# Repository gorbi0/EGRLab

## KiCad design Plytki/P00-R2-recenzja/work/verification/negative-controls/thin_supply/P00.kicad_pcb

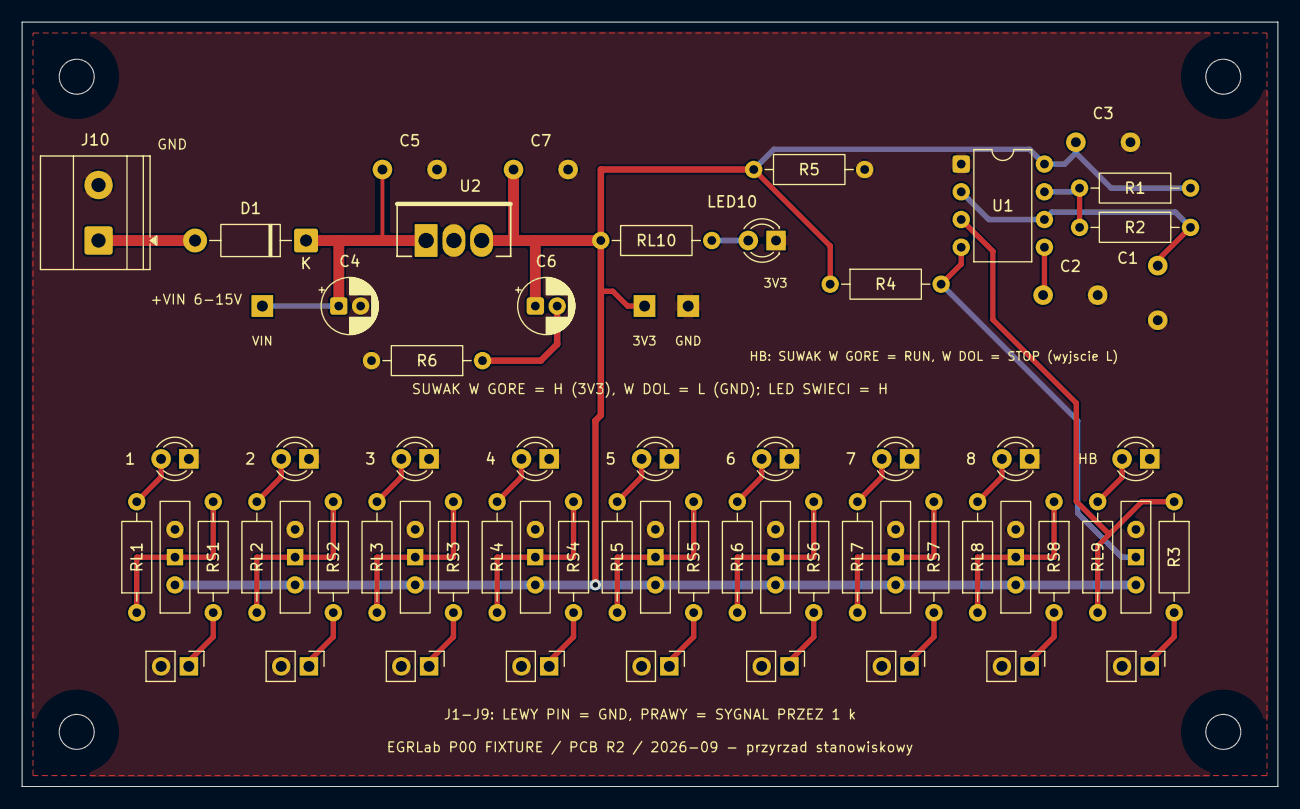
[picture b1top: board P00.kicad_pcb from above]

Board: 2 copper layers, 115.0 x 70.0 mm, 70 parts (0 on the bottom side), 37 nets.

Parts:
C1, C3, C5, C7: 100nF / X7R; C_Vishay_K15_H5_P5
C2: 10nF / X7R; C_Vishay_K15_H5_P5
C4: 10u / 50V; CP_Radial_D5.0mm_P2.00mm
C6: 22u / 50V; CP_Radial_D5.0mm_P2.00mm
D1: 1N5819; D_DO-41_SOD81_P10.16mm_Horizontal
H1, H2, H3, H4: M3 NPTH
J1: CH1 / pin header 1x2; PinHeader_1x02_P2.54mm_Vertical
J2: CH2 / pin header 1x2; PinHeader_1x02_P2.54mm_Vertical
J3: CH3 / pin header 1x2; PinHeader_1x02_P2.54mm_Vertical
J4: CH4 / pin header 1x2; PinHeader_1x02_P2.54mm_Vertical
J5: CH5 / pin header 1x2; PinHeader_1x02_P2.54mm_Vertical
J6: CH6 / pin header 1x2; PinHeader_1x02_P2.54mm_Vertical
J7: CH7 / pin header 1x2; PinHeader_1x02_P2.54mm_Vertical
J8: CH8 / pin header 1x2; PinHeader_1x02_P2.54mm_Vertical
J9: HEART / pin header 1x2; PinHeader_1x02_P2.54mm_Vertical
J10: VIN 6-15V / MKDS 2p; TerminalBlock_Phoenix_MKDS-1,5-2-5.08_1x02_P5.08mm_Horizont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
LED1: GREEN 3mm / CH1; LED_D3.0mm
LED2: GREEN 3mm / CH2; LED_D3.0mm
LED3: GREEN 3mm / CH3; LED_D3.0mm
LED4: GREEN 3mm / CH4; LED_D3.0mm
LED5: GREEN 3mm / CH5; LED_D3.0mm
LED6: GREEN 3mm / CH6; LED_D3.0mm
LED7: GREEN 3mm / CH7; LED_D3.0mm
LED8: GREEN 3mm / CH8; LED_D3.0mm
LED9: YELLOW 3mm / HEART; LED_D3.0mm
LED10: RED 3mm / 3V3; LED_D3.0mm
R1: 4K7 / 1%; R_Axial_DIN0207_L6.3mm_D2.5mm_P10.16mm_Horizontal
R2: 68K / 1%; R_Axial_DIN0207_L6.3mm_D2.5mm_P10.16mm_Horizontal
R3: 1K / 1%; R_Axial_DIN0207_L6.3mm_D2.5mm_P10.16mm_Horizontal
R4: 100K / 1%; R_Axial_DIN0207_L6.3mm_D2.5mm_P10.16mm_Horizontal
R5: 560R / 1%; R_Axial_DIN0207_L6.3mm_D2.5mm_P10.16mm_Horizontal
R6: 1R / 1%; R_Axial_DIN0207_L6.3mm_D2.5mm_P10.16mm_Horizontal
RL1, RL2, RL3, RL4, RL5, RL6, RL7, RL8, RL9, RL10: 1K / 1%; R_Axial_DIN0207_L6.3mm_D2.5mm_P10.16mm_Horizontal
RS1, RS2, RS3, RS4, RS5, RS6, RS7, RS8: 1K / 1%; R_Axial_DIN0207_L6.3mm_D2.5mm_P10.16mm_Horizontal
SW1: CH1 H/L; SW_Slide-03_Wuerth-WS-SLTV_10x2.5x6.4_P2.54mm
SW2: CH2 H/L; SW_Slide-03_Wuerth-WS-SLTV_10x2.5x6.4_P2.54mm
SW3: CH3 H/L; SW_Slide-03_Wuerth-WS-SLTV_10x2.5x6.4_P2.54mm
SW4: CH4 H/L; SW_Slide-03_Wuerth-WS-SLTV_10x2.5x6.4_P2.54mm
SW5: CH5 H/L; SW_Slide-03_Wuerth-WS-SLTV_10x2.5x6.4_P2.54mm
SW6: CH6 H/L; SW_Slide-03_Wuerth-WS-SLTV_10x2.5x6.4_P2.54mm
SW7: CH7 H/L; SW_Slide-03_Wuerth-WS-SLTV_10x2.5x6.4_P2.54mm
SW8: CH8 H/L; SW_Slide-03_Wuerth-WS-SLTV_10x2.5x6.4_P2.54mm
SW9: HEART RUN/STOP; SW_Slide-03_Wuerth-WS-SLTV_10x2.5x6.4_P2.54mm
TP1: V33; TestPad_1
TP2: GND; TestPad_1
TP3: VIN_P; TestPad_1
U1: TLC555CP; DIP-8_W7.62mm
U2: LM2937ET-3.3; TO220_3_P2.54_Drill1.4

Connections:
/P00_COUT_RET: C6.2, R6.1
/P00_CTRL: C2.1, U1.5
/P00_DIS: R1.2, R2.1, U1.7
/P00_HEART: J9.1, R3.2
/P00_LED1: LED1.2, RL1.2
/P00_LED2: LED2.2, RL2.2
/P00_LED3: LED3.2, RL3.2
/P00_LED4: LED4.2, RL4.2
/P00_LED5: LED5.2, RL5.2
/P00_LED6: LED6.2, RL6.2
/P00_LED7: LED7.2, RL7.2
/P00_LED8: LED8.2, RL8.2
/P00_LED_HB: LED9.2, RL9.2
/P00_LED_PWR: LED10.2, RL10.2
/P00_OSC: R3.1, RL9.1, U1.3
/P00_OUT1: J1.1, RS1.2
/P00_OUT2: J2.1, RS2.2
/P00_OUT3: J3.1, RS3.2
/P00_OUT4: J4.1, RS4.2
/P00_OUT5: J5.1, RS5.2
/P00_OUT6: J6.1, RS6.2
/P00_OUT7: J7.1, RS7.2
/P00_OUT8: J8.1, RS8.2
/P00_RC: C1.1, R2.2, U1.2, U1.6
/P00_RESET: R4.2, SW9.1, U1.4
/P00_S1: RL1.1, RS1.1, SW1.1
/P00_S2: RL2.1, RS2.1, SW2.1
/P00_S3: RL3.1, RS3.1, SW3.1
/P00_S4: RL4.1, RS4.1, SW4.1
/P00_S5: RL5.1, RS5.1, SW5.1
/P00_S6: RL6.1, RS6.1, SW6.1
/P00_S7: RL7.1, RS7.1, SW7.1
/P00_S8: RL8.1, RS8.1, SW8.1
/P00_V33: C3.1, C6.1, C7.1, R1.1, R4.1, R5.1, RL10.1, SW1.2, SW2.2, SW3.2, SW4.2, SW5.2, SW6.2, SW7.2, SW8.2, SW9.2, TP1.1, U1.8, U2.3
/P00_VIN: D1.2, J10.1
/P00_VIN_P: C4.1, C5.1, D1.1, TP3.1, U2.1
GND: C1.2, C2.2, C3.2, C4.2, C5.2, C7.2, J1.2, J2.2, J3.2, J4.2, J5.2, J6.2, J7.2, J8.2, J9.2, J10.2, LED1.1, LED2.1, LED3.1, LED4.1, LED5.1, LED6.1, LED7.1, LED8.1, LED9.1, LED10.1, R5.2, R6.2, SW1.3, SW2.3, SW3.3, SW4.3, SW5.3, SW6.3, SW7.3, SW8.3, SW9.3, TP2.1, U1.1, U2.2

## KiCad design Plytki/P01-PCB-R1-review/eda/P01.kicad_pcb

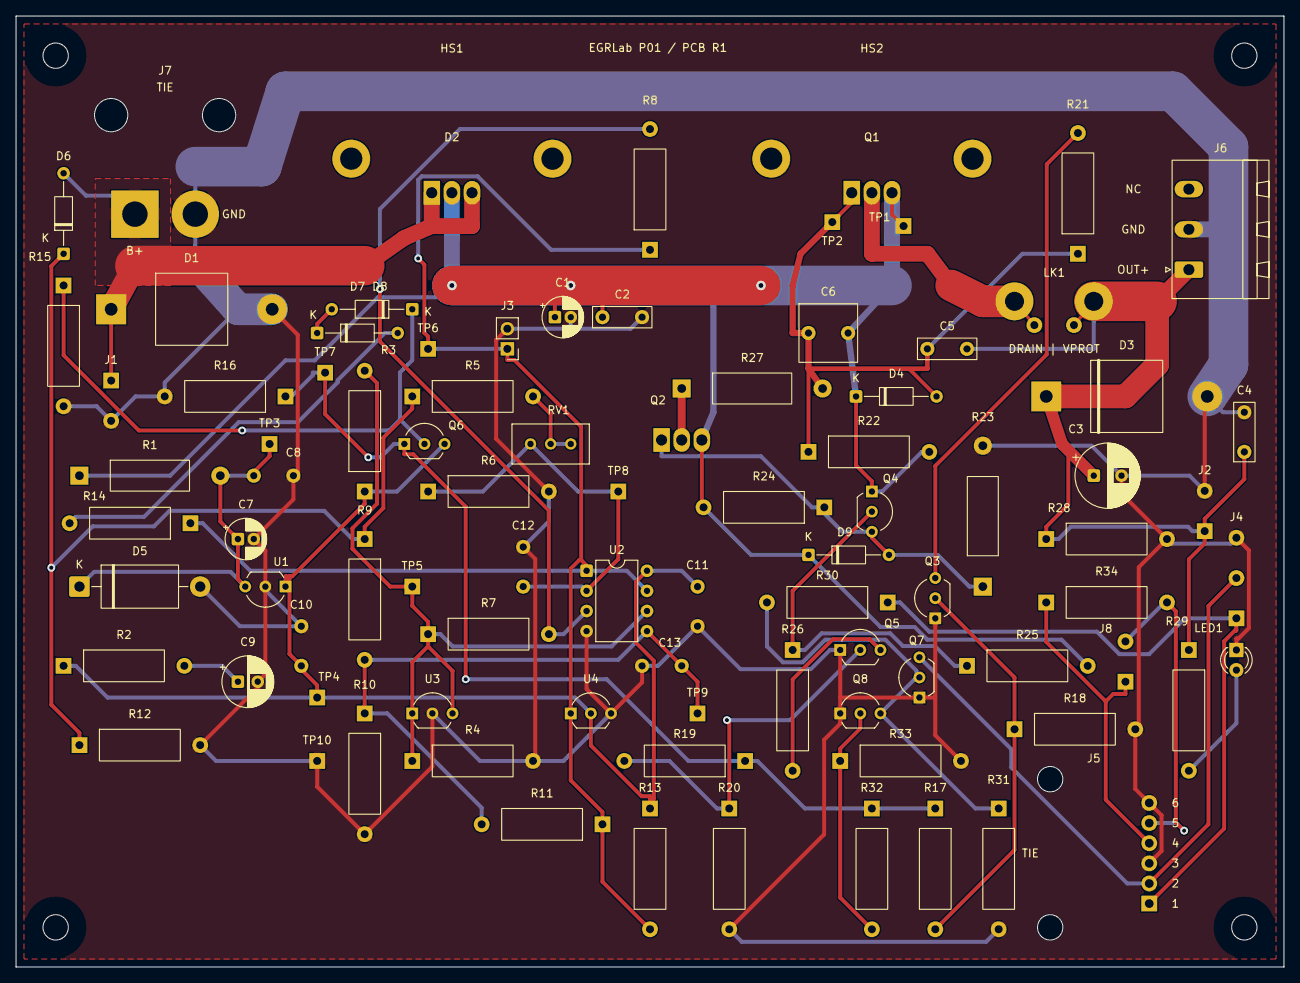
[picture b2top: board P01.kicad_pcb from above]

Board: 2 copper layers, 160.0 x 120.0 mm, 95 parts (0 on the bottom side), 34 nets.

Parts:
C1: 10u / 63V; CP_Radial_D5.0mm_P2.00mm
C2, C4: 100nF / 100V; C_TDK_B32529_L7.3_W2.5_P5
C3: 100u / 50V; CP_Radial_D8.0mm_P3.50mm
C5: 10nF / 100V; C_TDK_B32529_L7.3_W2.5_P5
C6: 1000nF / 100V; C_WIMA_MKS2_1u100V_L7.2_W7.2_P5
C7: 22u / 50V; CP_Radial_D5.0mm_P2.00mm
C8, C10, C11: 100nF / X7R; C_Vishay_K15_H5_P5
C9: 47u / 50V; CP_Radial_D6.3mm_P2.50mm
C12: 100pF / C0G; C_Vishay_K15_H5_P5
C13: 1nF / C0G; C_Vishay_K15_H5_P5
D1: 15KPA24CA; TVS_P600_BIDIR_P20.32
D2: STPS20100CT; TO220_3_P2.54_Drill1.4
D3: 5KP18A; TVS_P600_P20.32
D4: BZX55C15; D_DO-35_SOD27_P10.16mm_Horizontal
D5: 1.5KE18A-E3/54; D_DO-201_P15.24mm_Horizontal
D6, D7, D8: 1N4148; D_DO-35_SOD27_P10.16mm_Horizontal
D9: BZX55C15-TAP; D_DO-35_SOD27_P10.16mm_Horizontal
H1, H2, H3, H4: M3 NPTH
HS1, HS2: SK129-63STS; HS_Fischer_SK129_63.5_STS_D2.8
J1, J2, J8: TEST PADS; TestPads_2
J3: INHIBIT / SHORT=OFF; PinHeader_1x02_P2.54mm_Vertical
J4: TEST PADS; TestPads_3
J5: PG / soldered harness; Pigtail_PG_6xAWG22
J6: SUPPLY / MSTBA 3p; PhoenixContact_MSTBA_2,5_3-G-5,08_1x03_P5.08mm_Horizontal
J7: BAT / soldered wires; Pigtail_PWR_2x2.5mm2
LED1: GREEN 3mm; LED_D3.0mm
LK1: LINK / Cu 2.5mm2; Link_Kelvin_P10
Q1, Q2: SUP53P06-20-E3; TO220_3_P2.54_Drill1.4
Q3, Q5, Q6, Q7, Q8: 2N5551G; TO-92_Inline_Wide
Q4: 2N5401YBU; TO-92_Inline_Wide
R1: 150R / 2W; R_PR02_P17.78
R2: 1R / 0.5W; R_MFR50_H4_P15.24
R3: 820R / 0.5W; R_MFR50_H4_P15.24
R4, R16, R26, R30, R32: 10K / 0.5W; R_MFR50_H4_P15.24
R5: 54K9 / 0.1%; R_MFR50_H4_P15.24
R6, R7, R10: 10K / 0.1%; R_MFR50_H4_P15.24
R8: 220K / 0.1%; R_MFR50_H4_P15.24
R9: 26K1 / 0.1%; R_MFR50_H4_P15.24
R11: 249K / 0.1%; R_MFR50_H4_P15.24
R12, R15, R21, R24, R31: 100K / 0.5W; R_MFR50_H4_P15.24
R13: 2K2 / 0.5W; R_MFR50_H4_P15.24
R14, R17, R19, R28: 4K7 / 0.5W; R_MFR50_H4_P15.24
R18, R20, R25, R33: 47K / 0.5W; R_MFR50_H4_P15.24
R22: 470K / 0.5W; R_MFR50_H4_P15.24
R23: 2K2 / 2W; R_PR02_P17.78
R27: 10R / 2W; R_PR02_P17.78
R29: 6K8 / 0.5W; R_MFR50_H4_P15.24
R34: 0R / link; R_MFR50_H4_P15.24
RV1: 5K / 3296W; Potentiometer_Bourns_3296W_Vertical
TP1: VS; TestPad_1
TP2: GATE; TestPad_1
TP3: AUX_IN; TestPad_1
TP4: AUX5; TestPad_1
TP5: REF; TestPad_1
TP6: OK; TestPad_1
TP7: ENABLE; TestPad_1
TP8: OV_SENSE; TestPad_1
TP9: UV_SENSE; TestPad_1
TP10: GND; TestPad_1
U1: LM2936Z-5.0; TO-92_Inline_Wide
U2: LM2903P; DIP-8_W7.62mm
U3: TL431BILP; TO-92_Inline_Wide
U4: MCP120-450DI/TO; TO-92_Inline_Wide

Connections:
/AUX/P01_AUX_IN: C7.1, C8.1, D5.1, R1.2, TP3.1, U1.3
/AUX/P01_C_AUX_TOP: C9.1, R2.2
/AUX/P01_OV_REF: R7.2, R8.2, U2.3
/AUX/P01_OV_SENSE: C12.1, R6.1, RV1.3, TP8.1, U2.2
/AUX/P01_OV_TRIM_TOP: R5.2, RV1.1, RV1.2
/AUX/P01_REF: R3.2, R4.1, R7.1, TP5.1, U2.6, U3.1, U3.3
/AUX/P01_SENSE_RAW: D6.1, R5.1, R9.1, R12.1
/AUX/P01_UV_SENSE: C13.1, R9.2, R10.1, R11.2, TP9.1, U2.5
/P01_GATE: C5.1, C6.1, D4.2, Q1.1, R21.1, R22.1, R27.2, TP2.1
/P01_LED_A: LED1.2, R29.2
/P01_OFF_BASE: D9.2, Q2.1, Q4.3, R23.1, R24.1
/P01_OFF_COL: Q2.2, R27.1
/P01_ON_BASE: Q3.2, R17.2, R18.1
/P01_ON_COL: Q3.3, R21.2
/P01_Q1_DRAIN: LK1.1, Q1.2
/P01_RELEASE_BASE: Q5.2, R19.2, R20.1
/P01_RELEASE_COL: Q5.3, R26.2
/P01_RELEASE_PBASE: Q4.2, R25.1, R26.1
/SAFE/3V3_IO: J4.1, J5.1, R30.1
/SAFE/P01_BUF_BASE: D8.1, Q6.2, R15.1
/SAFE/P01_BUF_D1: D7.2, R14.2
/SAFE/P01_BUF_D2: D7.1, D8.2
/SAFE/P01_FAULT_BASE: Q7.2, Q8.3, R30.2, R31.1
/SAFE/P01_FAULT_RELEASE_BASE: Q8.2, R32.2, R33.1
/SAFE/PG_LINK: J5.5, J8.2, R34.2
/SAFE/PG_SEND: J5.4, J8.1, R34.1
/SAFE/SAFE_N: J4.2, J5.2, Q7.3
/VPROT: C3.1, C4.1, C5.2, D3.1, J2.1, J6.1, LK1.2, R28.1, R29.1
BAT_FUSED: D1.1, D2.1, D2.3, D6.2, J1.1, J7.1
GND: C1.2, C2.2, C3.2, C4.2, C7.2, C8.2, C9.2, C10.2, C11.2, C12.2, C13.2, D1.2, D3.2, D5.2, J1.2, J2.2, J3.2, J4.3, J5.3, J5.6, J6.2, J7.2, LED1.1, Q3.1, Q5.1, Q7.1, Q8.1, R4.2, R6.2, R10.2, R12.2, R15.2, R16.2, R18.2, R20.2, R23.2, R28.2, R31.2, R33.2, TP10.1, U1.2, U2.4, U3.2, U4.3
P01_AUX5: C10.1, C11.1, Q6.3, R2.1, R3.1, R13.1, TP4.1, U1.1, U2.8, U4.2
P01_ENABLE: Q6.1, R16.1, R17.1, R19.1, R32.1, TP7.1
P01_OK: J3.1, R8.1, R11.1, R13.2, R14.1, TP6.1, U2.1, U2.7, U4.1
P01_VS: C1.1, C2.1, C6.2, D2.2, D4.1, D9.1, Q1.3, Q2.3, Q4.1, R1.1, R22.2, R24.2, R25.2, TP1.1
